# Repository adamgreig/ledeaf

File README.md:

# LEDEAF

A modular LED light inspired by [@GeekMomProjects]' project. Compared to the
original, this version:

* is drawn from scratch in KiCad
* uses the attaching bolts for electrical contact, instead of spring contacts
* only requires one acrylic sheet per triangle
* all LEDs on each panel are driven by the same input data

[@GeekMomProjects]: https://twitter.com/GeekMomProjects/status/1269671840512794624

The project is designed for complete SMT assembly by JLCPCB.

## License

Hardware designs licensed under the [CERN-OHL-P v2].

[CERN-OHL-P v2]: LICENSE_CERN_OHL_P_v2.txt

> You may redistribute and modify this documentation and make products
> using it under the terms of the CERN-OHL-P v2 (https:/cern.ch/cern-ohl).
> This documentation is distributed WITHOUT ANY EXPRESS OR IMPLIED
> WARRANTY, INCLUDING OF MERCHANTABILITY, SATISFACTORY QUALITY
> AND FITNESS FOR A PARTICULAR PURPOSE. Please see the CERN-OHL-P v2
> for applicable conditions

Software licensed under the [Mozilla Public License].

[Mozilla Public License]: LICENSE_MPL.txt

> This Source Code Form is subject to the terms of the Mozilla Public
> License, v. 2.0. If a copy of the MPL was not distributed with this
> file, You can obtain one at https://mozilla.org/MPL/2.0/.

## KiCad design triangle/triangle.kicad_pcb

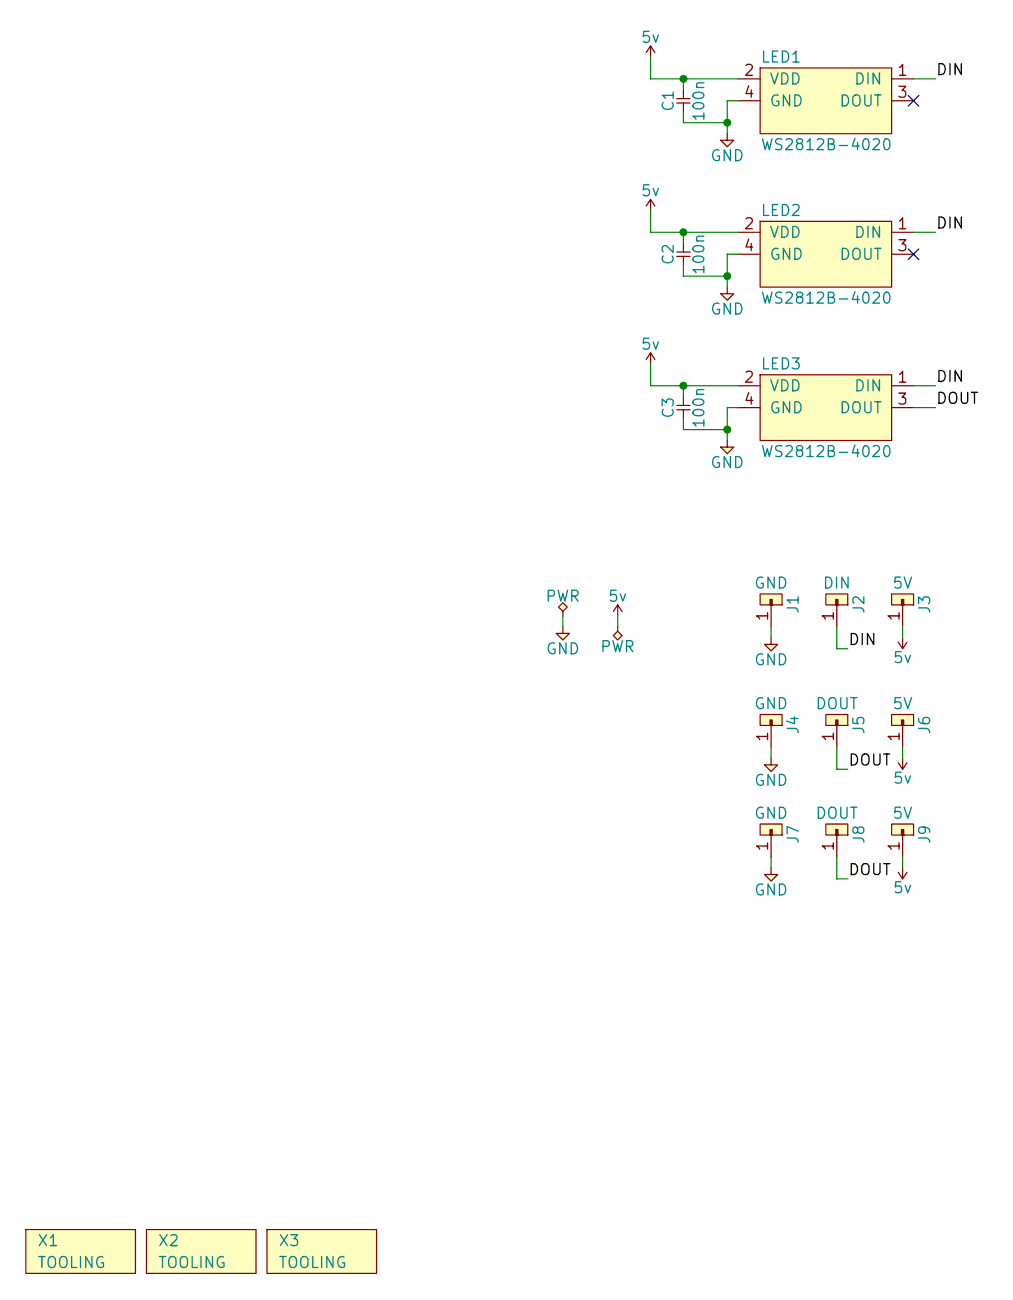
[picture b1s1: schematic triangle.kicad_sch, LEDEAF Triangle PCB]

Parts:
C1, C2, C3: 100n; 0402; LCSC C1525
J1, J4, J7: GND; M2_PTH
J2: DIN; M2_PTH
J3, J6, J9: 5V; M2_PTH
J5, J8: DOUT; M2_PTH
LED1, LED2, LED3: WS2812B-4020; LCSC C965557
X1, X2, X3: TOOLING; M2.5_HOLE

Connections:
5v: C1.2, C2.2, C3.2, J3.1, J6.1, J9.1, LED1.2 (VDD), LED2.2 (VDD), LED3.2 (VDD)
/DIN: J2.1, LED1.1 (DIN), LED2.1 (DIN), LED3.1 (DIN)
/DOUT: J5.1, J8.1, LED3.3 (DOUT)
GND: C1.1, C2.1, C3.1, J1.1, J4.1, J7.1, LED1.4 (GND), LED2.4 (GND), LED3.4 (GND)

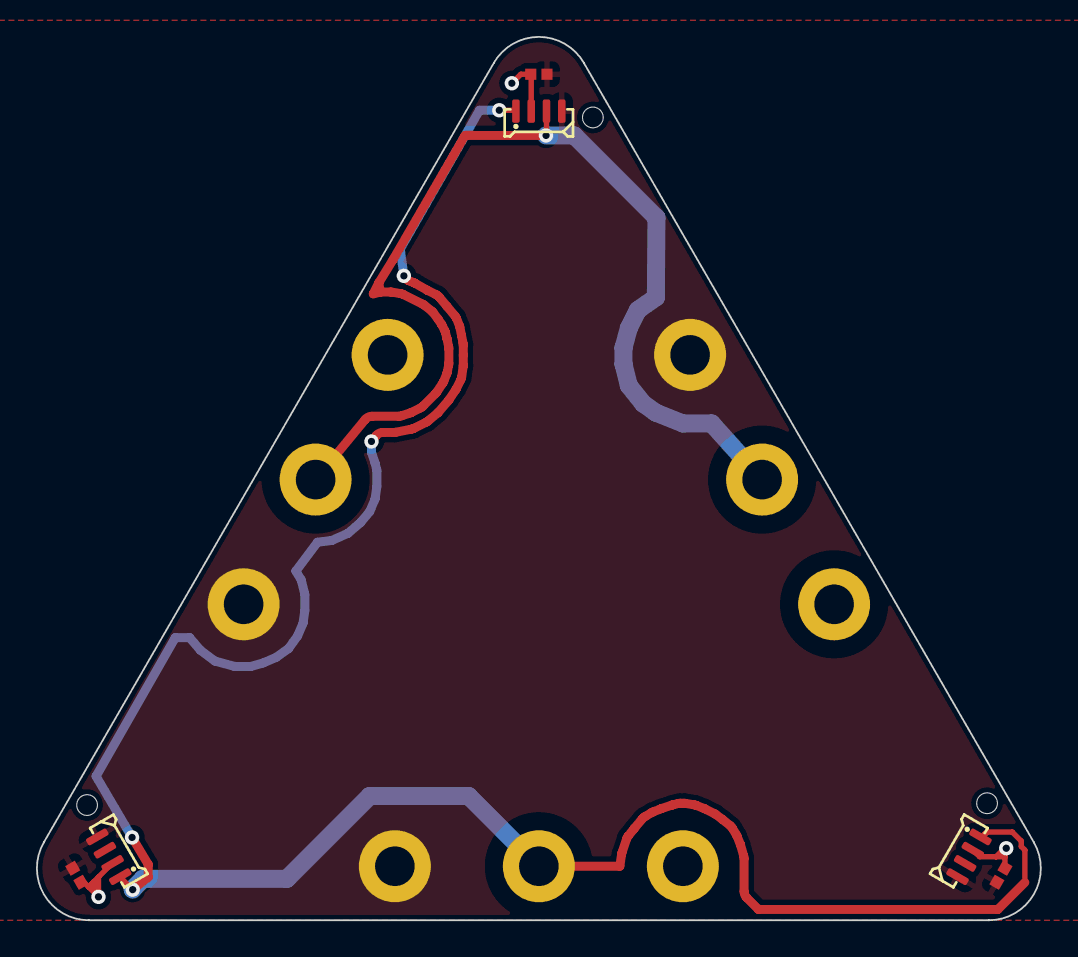
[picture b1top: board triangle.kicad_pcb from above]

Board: 2 copper layers, 55.8 x 49.1 mm, 18 parts (0 on the bottom side), 4 nets.

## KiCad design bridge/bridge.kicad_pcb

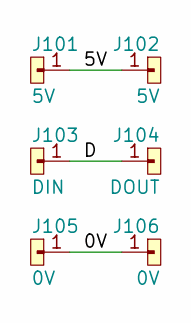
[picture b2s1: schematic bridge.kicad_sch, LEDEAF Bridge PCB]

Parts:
J101, J102: 5V; M2_PTH
J103: DIN; M2_PTH
J104: DOUT; M2_PTH
J105, J106: 0V; M2_PTH

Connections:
/0V: J105.1, J106.1
/5V: J101.1, J102.1
/D: J103.1, J104.1

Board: 2 copper layers, 6 parts (0 on the bottom side), 3 nets, no tracks yet.

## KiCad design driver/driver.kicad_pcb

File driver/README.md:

# ledeaf driver

This directory contains the PCB design for the driver board.

## Revision 1: 2021-05

### Errata

* Issue going into USB bootloader possibly because BOOT1 (PB2) is floating,
  maybe add a pull-down resistor.

### Thoughts For Next Rev

* Combine BOOTLOAD and PATTERN buttons into one (wire BOOT0 up to a GPIO)
  to reduce BOM count.
* Investigate cheaper STM32 and oscillator.
* Add light sensor to allow automatically scaling brightness.

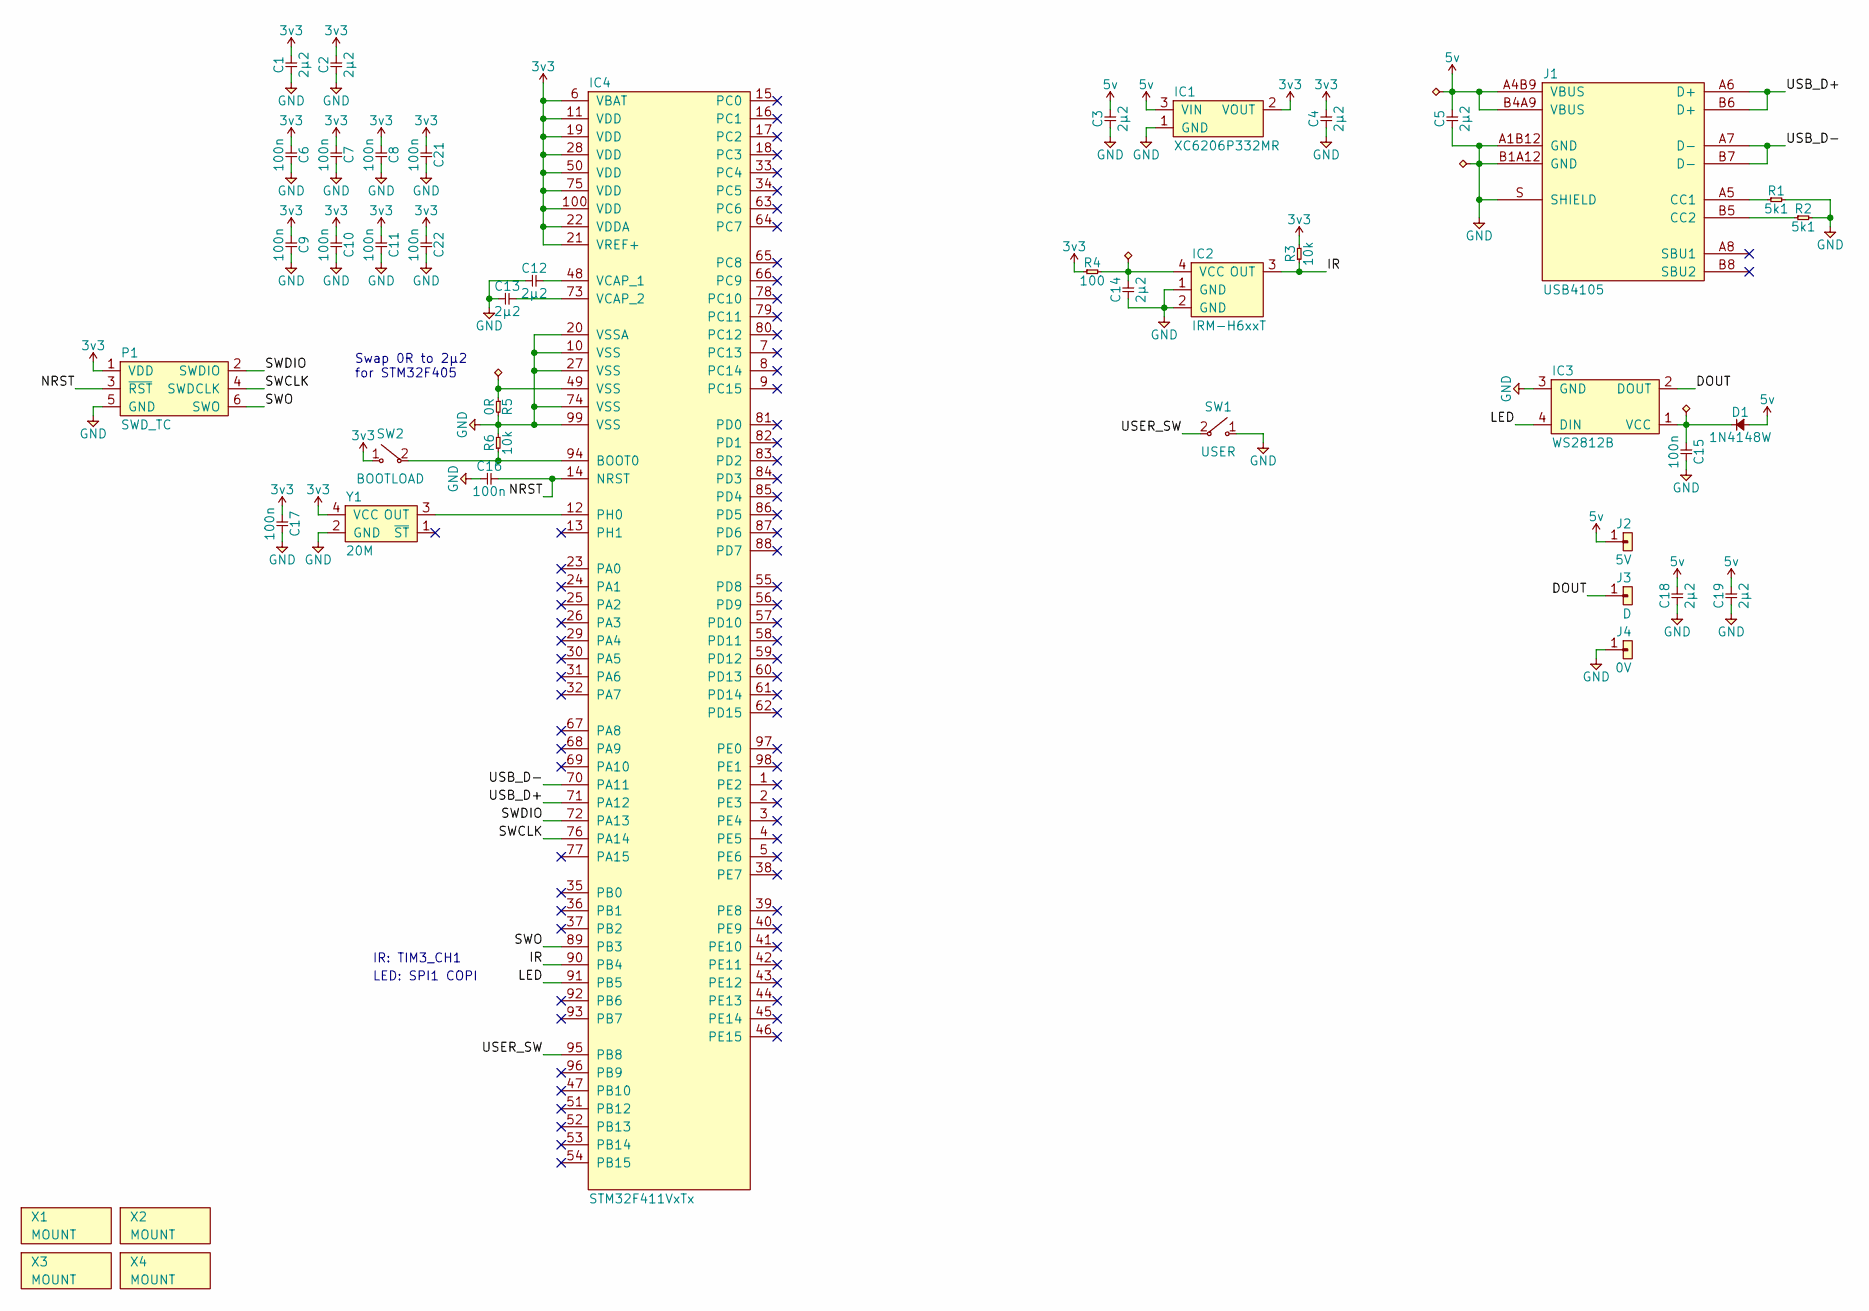
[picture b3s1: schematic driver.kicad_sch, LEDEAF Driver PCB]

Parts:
C1, C2, C3, C4, C5, C12, C13, C14, C18, C19: 2µ2; 0603; LCSC C23630
C6, C7, C8, C9, C10, C11, C15, C16, C17, C21, C22: 100n; 0402; LCSC C1525
D1: 1N4148W; SOD-123; LCSC C81598
IC1: XC6206P332MR; SOT-23; LCSC C5446
IC2: IRM-H6xxT; IRM-H6XXT; LCSC C390031
IC3: WS2812B; LCSC C114586
IC4: STM32F411VxTx; LQFP-100; LCSC C382005
J1: USB4105; LCSC C167321
J2: 5V; M2_PTH
J3: D; M2_PTH
J4: 0V; M2_PTH
P1: SWD_TC; TC2030-NL
R1, R2: 5k1; 0402; LCSC C25905
R3, R6: 10k; 0402; LCSC C25744
R4: 100; 0402; LCSC C25076
R5: 0R; 0603; LCSC C21189
SW1: USER; SW_MOM_6X6; LCSC C127509
SW2: BOOTLOAD; SW_MOM_6X6; LCSC C127509
X1, X2, X3, X4: MOUNT; M3_HOLE
Y1: 20M; XO-32x25; LCSC C32529

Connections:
3v3: C1.2, C2.2, C4.2, C6.1, C7.1, C8.1, C9.1, C10.1, C11.1, C17.1, C21.1, C22.1, IC1.2 (VOUT), IC4.6 (VBAT), IC4.11 (VDD), IC4.19 (VDD), IC4.21 (VREF+), IC4.22 (VDDA), IC4.28 (VDD), IC4.50 (VDD), IC4.75 (VDD), IC4.100 (VDD), P1.1 (VDD), R3.2, R4.1, SW2.1 ("~"), Y1.4 (VCC)
5v: C3.2, C5.2, C18.2, C19.2, D1.2, IC1.3 (VIN), J1.A4B9 (VBUS), J1.B4A9 (VBUS), J2.1
/DOUT: IC3.2 (DOUT), J3.1
/IR: IC2.3 (OUT), IC4.90 (PB4), R3.1
/LED: IC3.4 (DIN), IC4.91 (PB5)
/NRST: C16.2, IC4.14 (NRST), P1.3 (~RST)
/SWCLK: IC4.76 (PA14), P1.4 (SWDCLK)
/SWDIO: IC4.72 (PA13), P1.2 (SWDIO)
/SWO: IC4.89 (PB3), P1.6 (SWO)
/USB_D+: IC4.71 (PA12), J1.A6 (D+), J1.B6 (D+)
/USB_D-: IC4.70 (PA11), J1.A7 (D-), J1.B7 (D-)
/USER_SW: IC4.95 (PB8), SW1.2 ("~")
GND: C1.1, C2.1, C3.1, C4.1, C5.1, C6.2, C7.2, C8.2, C9.2, C10.2, C11.2, C12.1, C13.1, C14.1, C15.2, C16.1, C17.2, C18.1, C19.1, C21.2, C22.2, IC1.1 (GND), IC2.1 (GND), IC2.2 (GND), IC3.3 (GND), IC4.10 (VSS), IC4.20 (VSSA), IC4.27 (VSS), IC4.74 (VSS), IC4.99 (VSS), J1.A1B12 (GND), J1.B1A12 (GND), J1.S (SHIELD), J4.1, P1.5 (GND), R1.2, R2.2, R5.2, R6.2, SW1.1 ("~"), Y1.2 (GND)
unnamed: C12.2, IC4.48 (VCAP_1)
unnamed: C13.2, IC4.73 (VCAP_2)
unnamed: C14.2, IC2.4 (VCC), R4.2
unnamed: C15.1, D1.1, IC3.1 (VCC)
unnamed: J1.A5 (CC1), R1.1
unnamed: J1.B5 (CC2), R2.1
unnamed: IC4.49 (VSS), R5.1
unnamed: IC4.94 (BOOT0), R6.1, SW2.2 ("~")
unnamed: IC4.12 (PH0), Y1.3 (OUT)

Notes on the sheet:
Swap 0R to 2µ2 for STM32F405
IR: TIM3_CH1
LED: SPI1 COPI

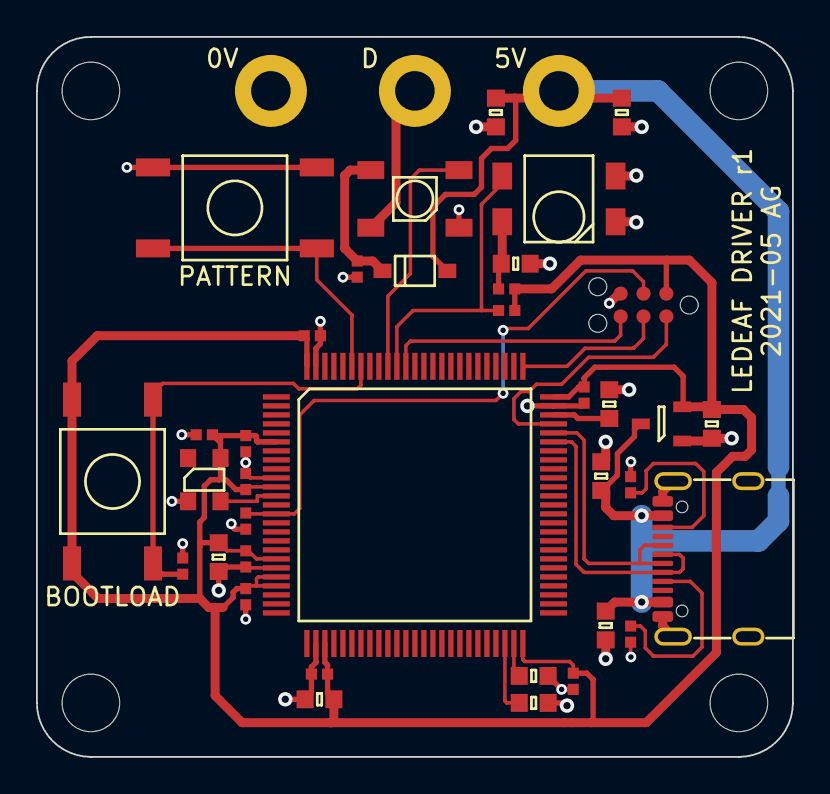
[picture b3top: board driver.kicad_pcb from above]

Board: 2 copper layers, 42.0 x 40.0 mm, 44 parts (0 on the bottom side), 22 nets.

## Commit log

2021-05-23 Initial commit. First version of triangle PCB.
2021-05-23 Add tooling holes
2021-05-23 Update triangle board to put LED centroid at footprint origin
2021-05-23 Add nightly version of bridge, but probably soon to be deleted
2021-05-23 Update bridge to use rectangular PCB for v-score
2021-05-23 Add driver PCB
2021-05-23 Update page info boxes
2021-05-23 Add renders, PDFs, README
2021-05-23 Add WS2812-4020 3d model, update render
2021-06-03 Add first demo firmware
2021-06-03 Add prototype laser cut cover
2021-06-05 Swap to saturating_sub
2021-06-05 Add 100x150 sheet for laser cutting
2021-06-24 Remove bounding box from laser cut 100x150 sheet
2021-06-26 Add 300x300 sheet of laser covers, add 3d printed base mount
2021-06-26 Try out using choreographer to sequence the LEDs
2021-06-27 Extend SysTick to 32bit using a separate static atomic
2021-06-27 Revert extended SysTick
2021-06-27 Fix max number of states in each sequence
2021-06-27 Use heapless::Vec to simplify creating actions
2021-06-27 Add README for driver PCB
2021-06-27 Add some more READMEs, update cover.dxf to new M2-clear third hole design, licence firmware under MPL2, tidy up firmware.
2021-06-27 Implement IR decoder
2021-06-27 Swap to 100fps fixed-rate rendering
2021-06-27 Use Sequence::new_array instead of default as it's const
2021-06-27 Swap to a 32-bit TIM5 instead of SysTick for timebase; extract IR decoding into its own module.
2021-06-27 Move logs into target directory
2021-06-27 Refactor timer and IR stuff out of main.rs
2021-06-27 Further refactoring and create multiple patterns.
2021-06-27 Write ARR for TIM3 and TIM5 explicitly
2021-06-27 Add some photos
2021-06-27 Resize bottom.png to match top.png
2021-06-27 Resize top.png to match bottom.png
2021-06-27 Update 001_lit_up.jpg with better pic
2021-06-27 Update README with extra license details
2021-06-27 Add IR repeated command handling
2021-06-27 Timeout last_cmd after 200ms
2021-07-01 Use new IR protocol and commands, add new patterns.
2021-07-01 Update cut order on cover_100x150
